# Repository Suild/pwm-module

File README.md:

# pwm-module
Schematics and board files for every variant (including prototypes) of the PWM module

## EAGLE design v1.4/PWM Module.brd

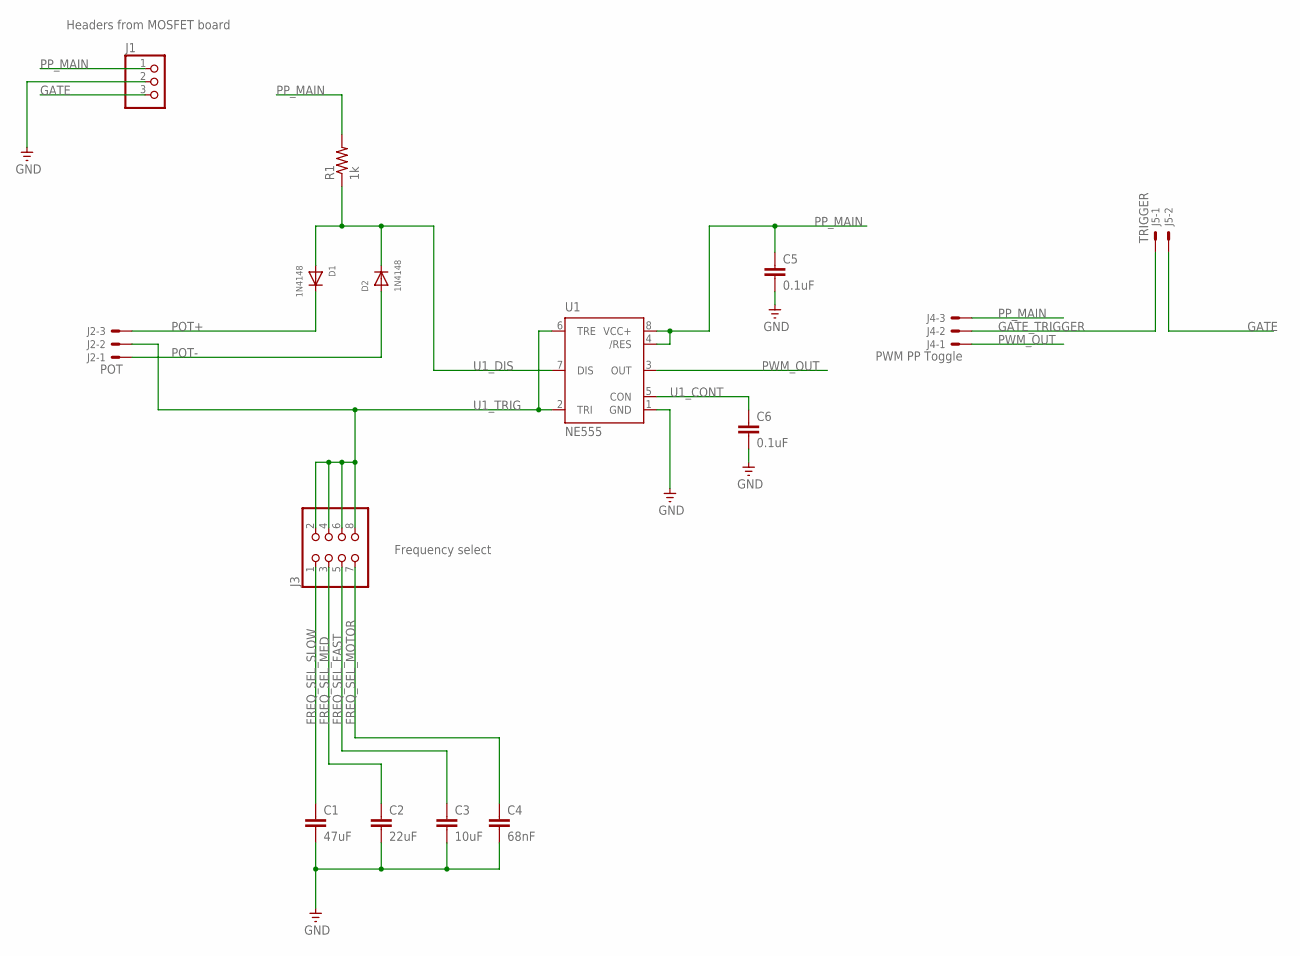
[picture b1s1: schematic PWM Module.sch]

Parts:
C1: 47uF; C1210
C2: 22uF; C1206
C3: 10uF; C1206
C4: 68nF; C0805
C5, C6: 0.1uF; C0805
D1, D2: 1N4148; DO-1N4148
J1: PINHD-1X3; 1X03
J2: POT; JST-XH-03-PACKAGE-LONG-PAD
J3: PINHD-2X4; 2X04
J4: PWM PP Toggle; JST-XH-03-PACKAGE-LONG-PAD
J5: TRIGGER; JST-XH-02-PACKAGE-LONG-PAD
R1: 1k; R0805
U1: NE555; DIL-08

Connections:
FREQ_SEL_FAST: C3.1, J3.5
FREQ_SEL_MED: C2.1, J3.3
FREQ_SEL_MOTOR: C4.1, J3.7
FREQ_SEL_SLOW: C1.1, J3.1
GATE: J1.3, J5.2
GATE_TRIGGER: J4.2, J5.1
GND: C1.2, C2.2, C3.2, C4.2, C5.2, C6.2, J1.2, U1.1 (GND)
POT+: D1.C, J2.3
POT-: D2.A, J2.1
PP_MAIN: C5.1, J1.1, J4.3, R1.2, U1.4 (/RES), U1.8 (VCC+)
PWM_OUT: J4.1, U1.3 (OUT)
U1_CONT: C6.1, U1.5 (CON)
U1_DIS: D1.A, D2.C, R1.1, U1.7 (DIS)
U1_TRIG: J2.2, J3.2, J3.4, J3.6, J3.8, U1.2 (TRI), U1.6 (TRE)

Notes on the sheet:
Headers from MOSFET board
Frequency select

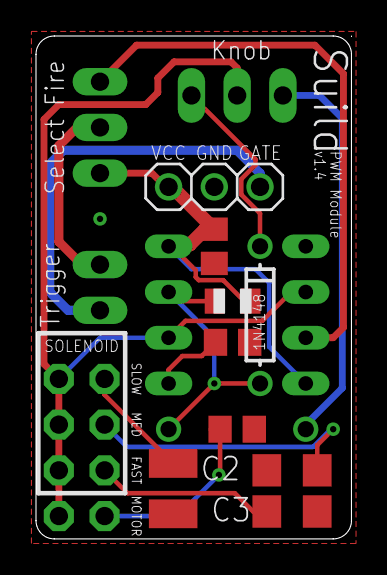
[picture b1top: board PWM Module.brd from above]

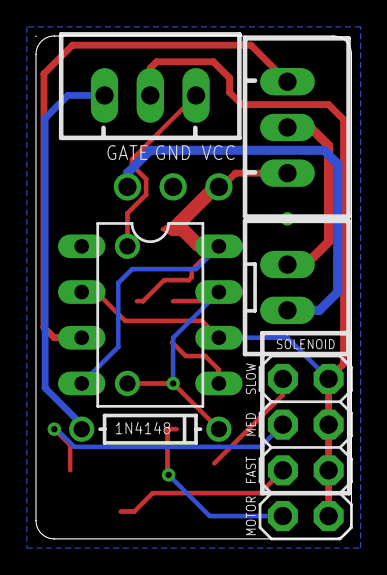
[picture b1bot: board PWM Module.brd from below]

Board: 2 copper layers, 17.5 x 27.9 mm, 15 parts (6 on the bottom side), 14 nets.

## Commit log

2019-10-26 add files for PWM Module v1.4
2020-04-08 add wiring diagram for wiring up a solenoid and flywheel combo
